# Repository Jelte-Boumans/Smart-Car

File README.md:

# Smart-Car
* Analyse bevat alle files die behoren tot de analyse van dit project
* Code bavat alle software geschreven voor dit project
* Schemas bevat alle versies van de schemas en PCBs voor dit project

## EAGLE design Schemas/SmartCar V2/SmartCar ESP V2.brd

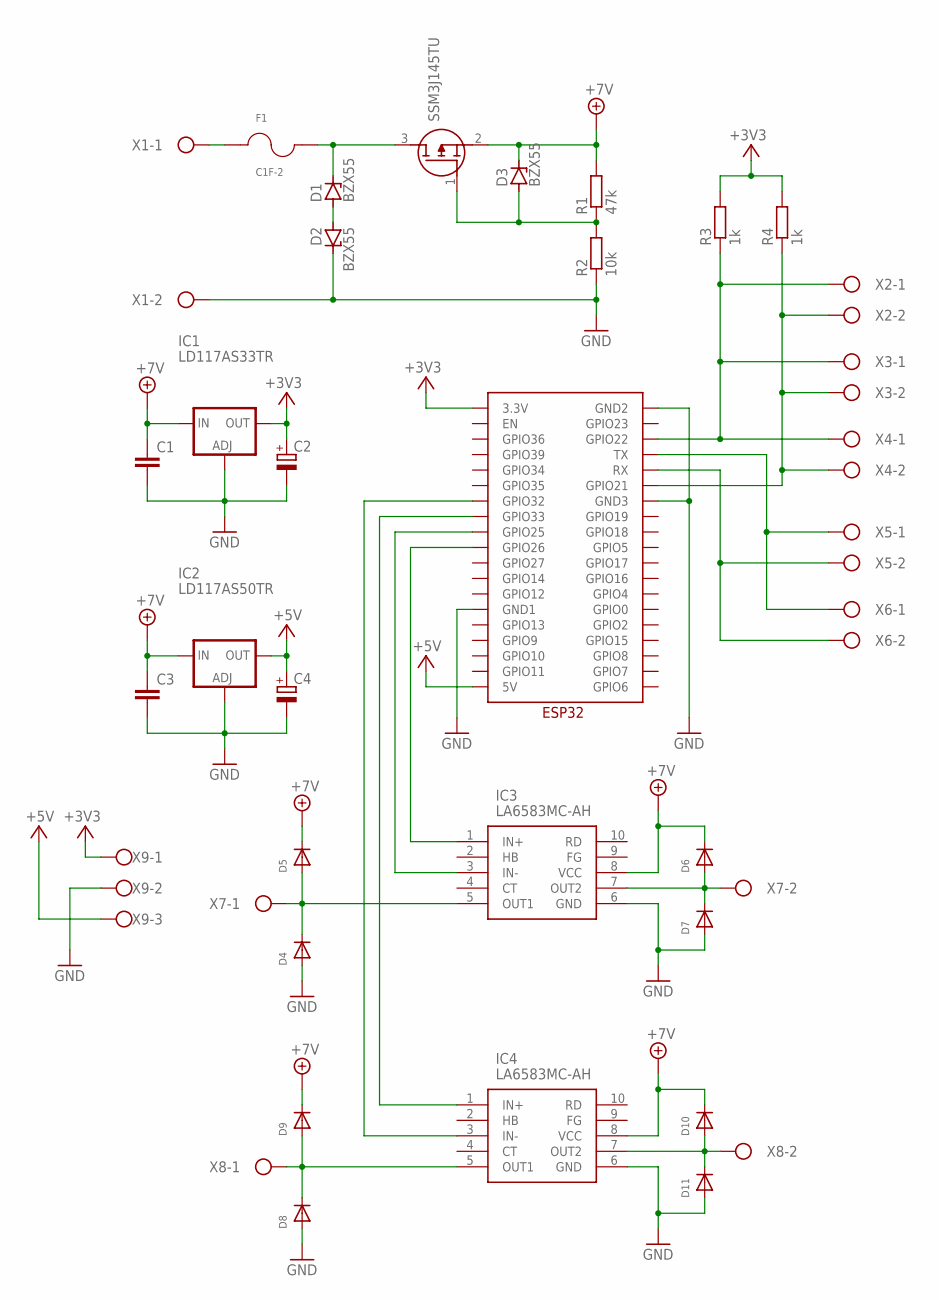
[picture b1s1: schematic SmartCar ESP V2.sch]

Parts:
C1, C3: C-EUC0805; C0805
C2, C4: CPOL-EUE2,5-6E; E2,5-6E
D1, D2, D3: BZX55; DO35Z10
D4, D5, D6, D7, D8, D9, D10, D11: DIODESMA; SMADIODE
F1: C1F-2; FUSC3215X83N
IC1: LD117AS33TR; SOT223
IC2: LD117AS50TR; SOT223
IC3, IC4: LA6583MC-AH; SOP100P620X155-10N
R1: 47k; R0805
R2: 10k; R0805
R3, R4: 1k; R0805
U$1: ESP32
U$2: SSM3J145TU; SOTFL65P210X75-3N
X1, X2, X3, X4, X5, X6, X7, X8: W237-102
X9: W237-103

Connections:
+3V3: C2.+, IC1.4 (OUT), R3.2, R4.2, U$1.3.3V, X9.1
+5V: C4.+, IC2.4 (OUT), U$1.5V, X9.3
+7V: C1.1, C3.1, D3.C, D5.C, D6.C, D9.C, D10.C, IC1.3 (IN), IC2.3 (IN), IC3.8 (VCC), IC4.8 (VCC), R1.2, U$2.2 (S)
GND: C1.2, C2.-, C3.2, C4.-, D2.C, D4.A, D7.A, D8.A, D11.A, IC1.1 (ADJ), IC2.1 (ADJ), IC3.6 (GND), IC4.6 (GND), R2.1, U$1.GND1, U$1.GND2, U$1.GND3, X1.2, X9.2
unnamed: F1.1, X1.1
unnamed: D1.A, D2.A
unnamed: D1.C, F1.2, U$2.3 (D)
unnamed: R4.1, U$1.GPIO21, X2.2, X3.2, X4.2
unnamed: U$1.TX, X5.1, X6.1
unnamed: D3.A, R1.1, R2.2, U$2.1 (G)
unnamed: R3.1, U$1.GPIO22, X2.1, X3.1, X4.1
unnamed: D4.C, D5.A, IC3.5 (OUT1), X7.1
unnamed: D6.A, D7.C, IC3.7 (OUT2), X7.2
unnamed: D10.A, D11.C, IC4.7 (OUT2), X8.2
unnamed: D8.C, D9.A, IC4.5 (OUT1), X8.1
unnamed: IC3.1 (IN+), U$1.GPIO26
unnamed: IC3.3 (IN-), U$1.GPIO25
unnamed: IC4.1 (IN+), U$1.GPIO33
unnamed: IC4.3 (IN-), U$1.GPIO32
unnamed: U$1.RX, X5.2, X6.2

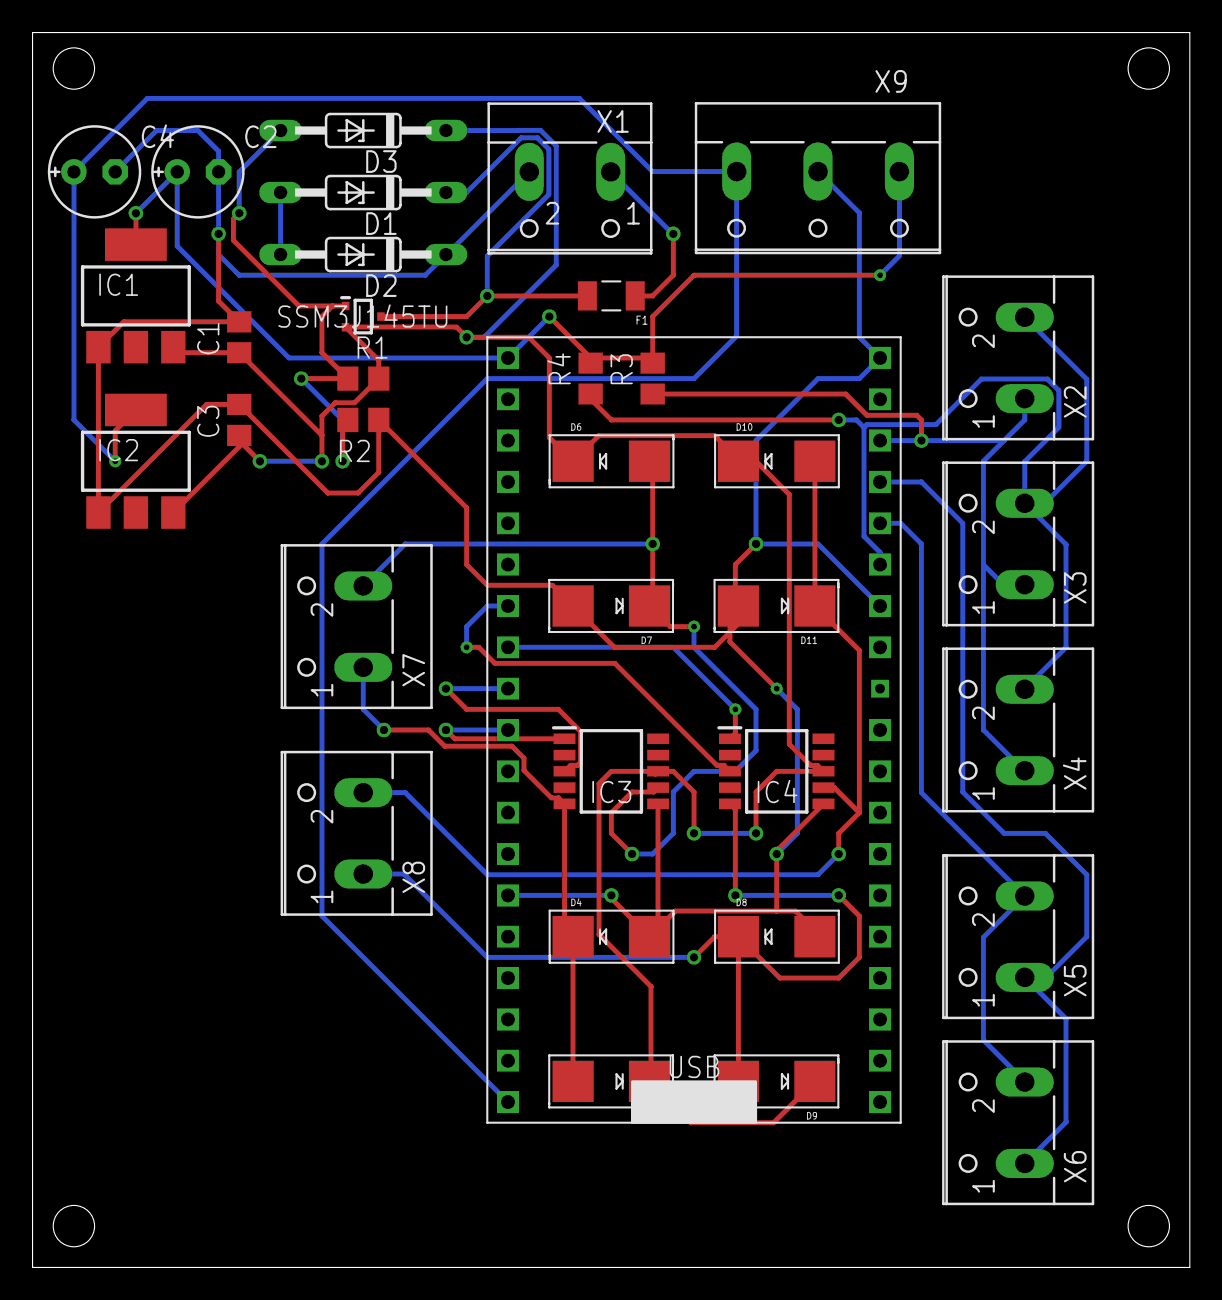
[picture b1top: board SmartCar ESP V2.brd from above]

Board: 2 copper layers, 71.1 x 75.9 mm, 35 parts (0 on the bottom side), 20 nets.

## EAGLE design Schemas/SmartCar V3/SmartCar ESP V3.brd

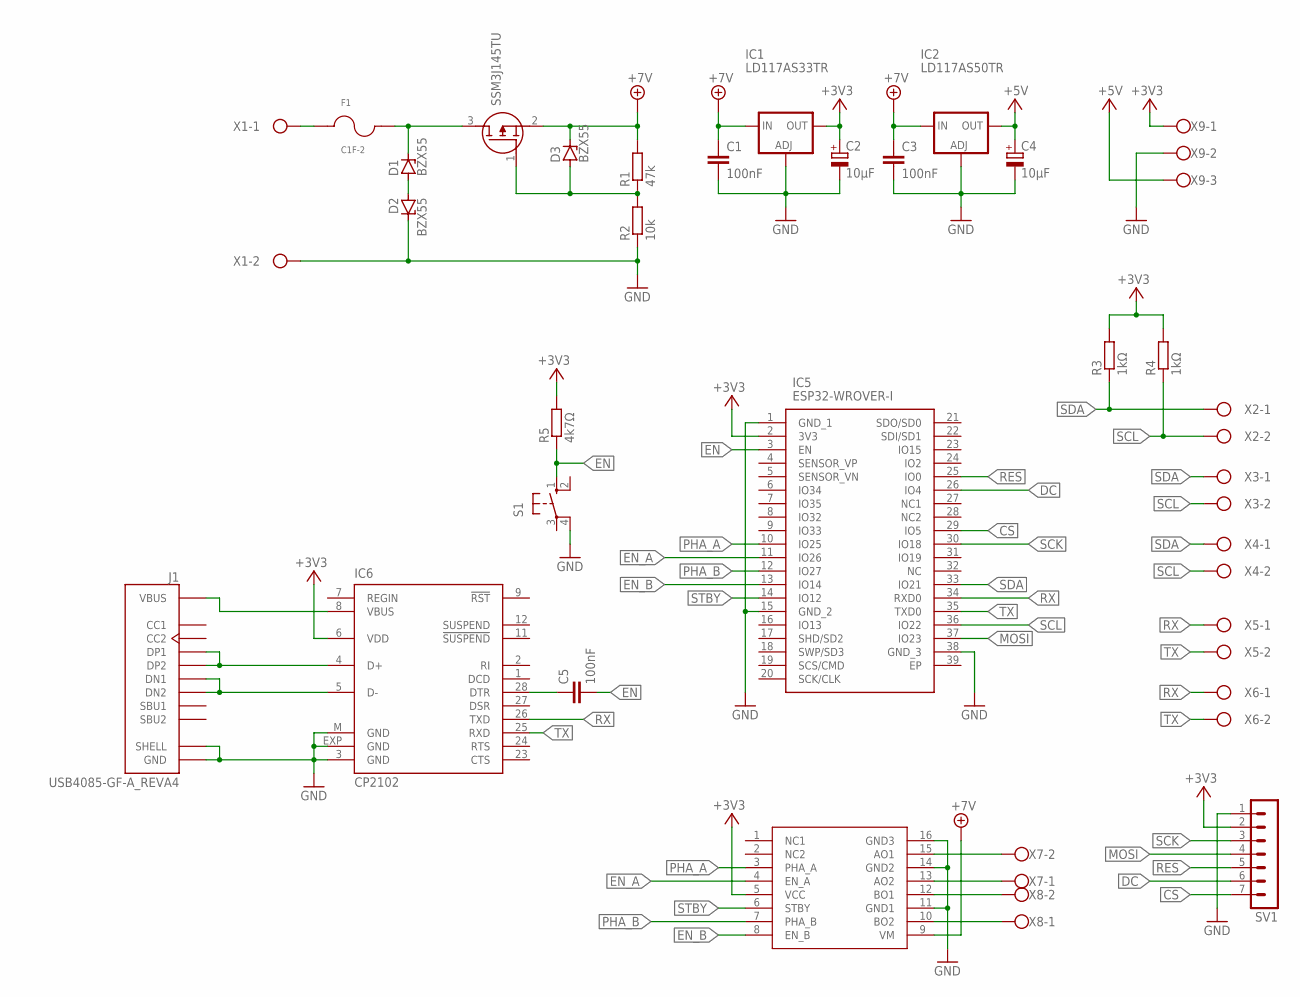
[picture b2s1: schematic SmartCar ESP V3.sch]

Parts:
C1, C3, C5: 100nF; C0805
C2, C4: 10µF; E2,5-6E
D1, D2, D3: BZX55; DO35Z10
F1: C1F-2; FUSC3215X83N
IC1: LD117AS33TR; SOT223
IC2: LD117AS50TR; SOT223
IC5: ESP32-WROVER-I; ESP32WROVERI
IC6: CP2102; MLP28
J1: USB4085-GF-A_REVA4; GCT_USB4085-GF-A_REVA4
R1: 47k; R0805
R2: 10k; R0805
R3, R4: 1kΩ; R0805
R5: 4k7Ω; R0805
S1: 10-XX; B3F-10XX
SV1: MA07-1
U$1: TC78H621FNG; SOP65P640X110-16N
U$2: SSM3J145TU; SOTFL65P210X75-3N
X1, X2, X3, X4, X5, X6, X7, X8: W237-102
X9: W237-103

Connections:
+3V3: C2.+, IC1.4 (OUT), IC5.2 (3V3), IC6.6 (VDD), R3.2, R4.2, R5.2, SV1.2, U$1.5 (VCC), X9.1
+5V: C4.+, IC2.4 (OUT), X9.3
+7V: C1.1, C3.1, D3.C, IC1.3 (IN), IC2.3 (IN), R1.2, U$1.9 (VM), U$2.2 (S)
CS: IC5.29 (IO5), SV1.7
DC: IC5.26 (IO4), SV1.6
EN: C5.2, IC5.3 (EN), R5.1, S1.1 (S)
EN_A: IC5.11 (IO26), U$1.4 (EN_A)
EN_B: IC5.13 (IO14), U$1.8 (EN_B)
GND: C1.2, C2.-, C3.2, C4.-, D2.C, IC1.1 (ADJ), IC2.1 (ADJ), IC5.1 (GND_1), IC5.15 (GND_2), IC5.38 (GND_3), IC6.3 (GND), IC6.EXP (GND), IC6.M (GND), J1.A1 (GND), J1.A12 (GND), J1.B1 (GND), J1.B12 (GND), J1.P1 (SHELL), J1.P2 (SHELL), J1.P3 (SHELL), J1.P4 (SHELL), R2.1, S1.4 (P1), SV1.1, U$1.11 (GND1), U$1.14 (GND2), U$1.16 (GND3), X1.2, X9.2
MOSI: IC5.37 (IO23), SV1.4
unnamed: F1.1, X1.1
unnamed: D1.A, D2.A
unnamed: D1.C, F1.2, U$2.3 (D)
unnamed: IC6.5 (D-), J1.A7 (DN1), J1.B7 (DN2)
unnamed: IC6.4 (D+), J1.A6 (DP1), J1.B6 (DP2)
unnamed: C5.1, IC6.28 (DTR)
unnamed: D3.A, R1.1, R2.2, U$2.1 (G)
unnamed: U$1.15 (AO1), X7.2
unnamed: U$1.13 (AO2), X7.1
unnamed: U$1.12 (BO1), X8.2
unnamed: U$1.10 (BO2), X8.1
unnamed: IC6.8 (VBUS), J1.A4 (VBUS), J1.A9 (VBUS), J1.B4 (VBUS), J1.B9 (VBUS)
PHA_A: IC5.10 (IO25), U$1.3 (PHA_A)
PHA_B: IC5.12 (IO27), U$1.7 (PHA_B)
RES: IC5.25 (IO0), SV1.5
RX: IC5.34 (RXD0), IC6.26 (TXD), X5.1, X6.1
SCK: IC5.30 (IO18), SV1.3
SCL: IC5.36 (IO22), R4.1, X2.2, X3.2, X4.2
SDA: IC5.33 (IO21), R3.1, X2.1, X3.1, X4.1
STBY: IC5.14 (IO12), U$1.6 (STBY)
TX: IC5.35 (TXD0), IC6.25 (RXD), X5.2, X6.2

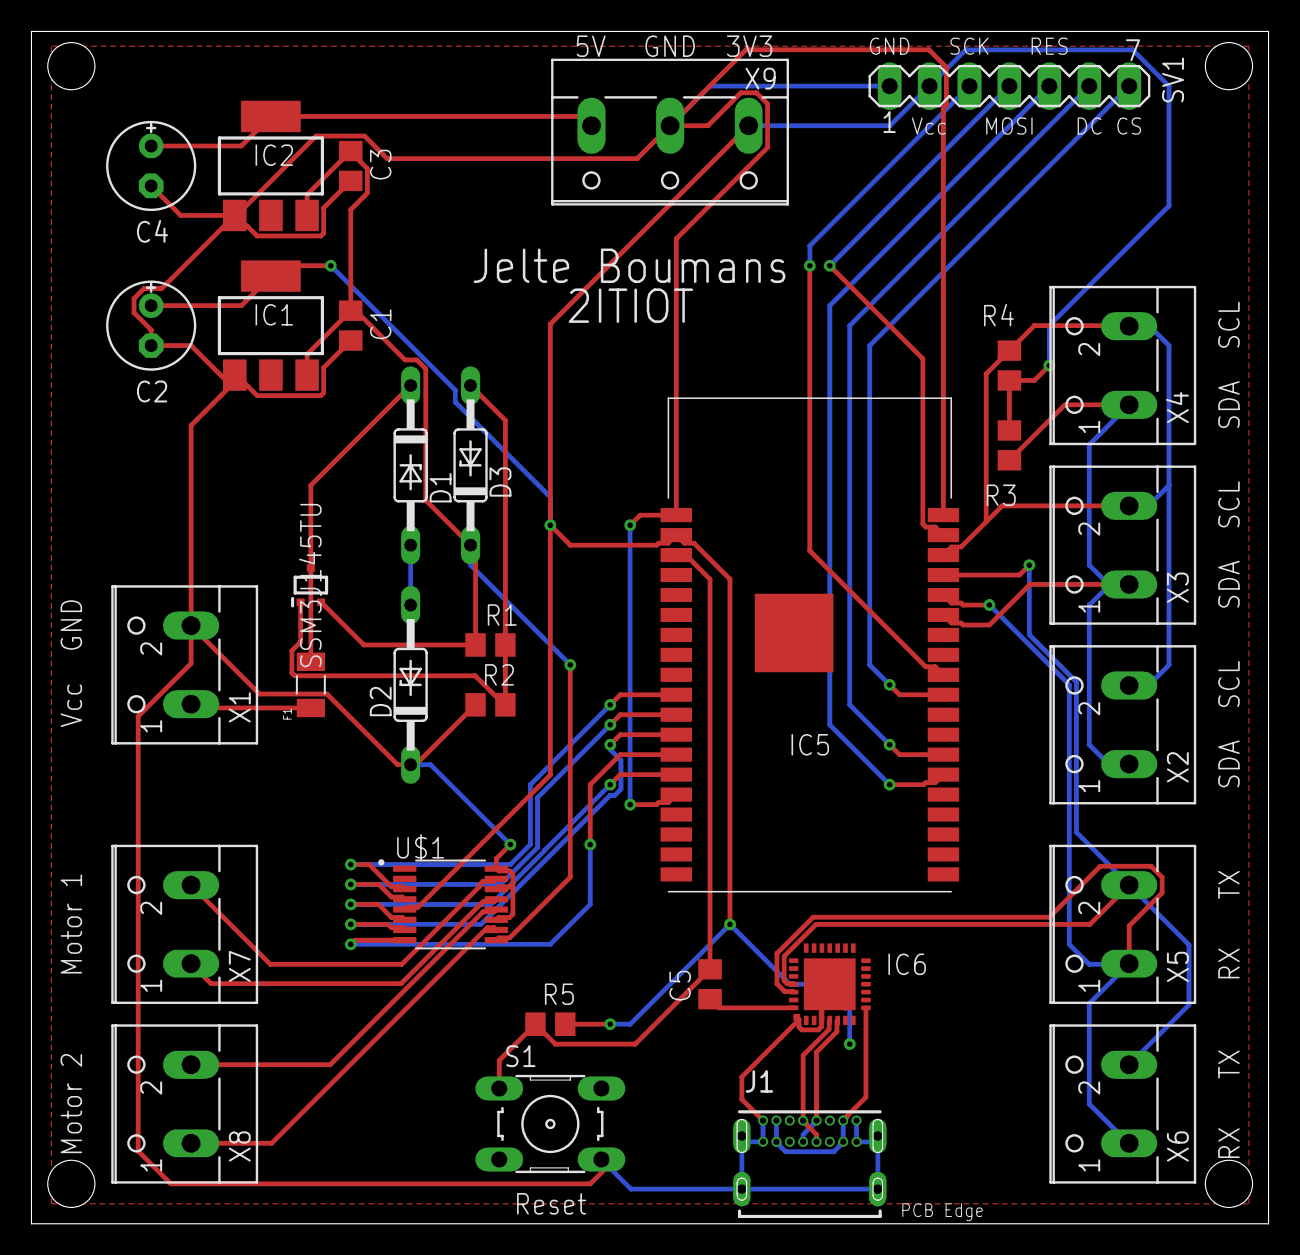
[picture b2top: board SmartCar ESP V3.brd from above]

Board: 2 copper layers, 78.7 x 75.9 mm, 32 parts (0 on the bottom side), 31 nets.

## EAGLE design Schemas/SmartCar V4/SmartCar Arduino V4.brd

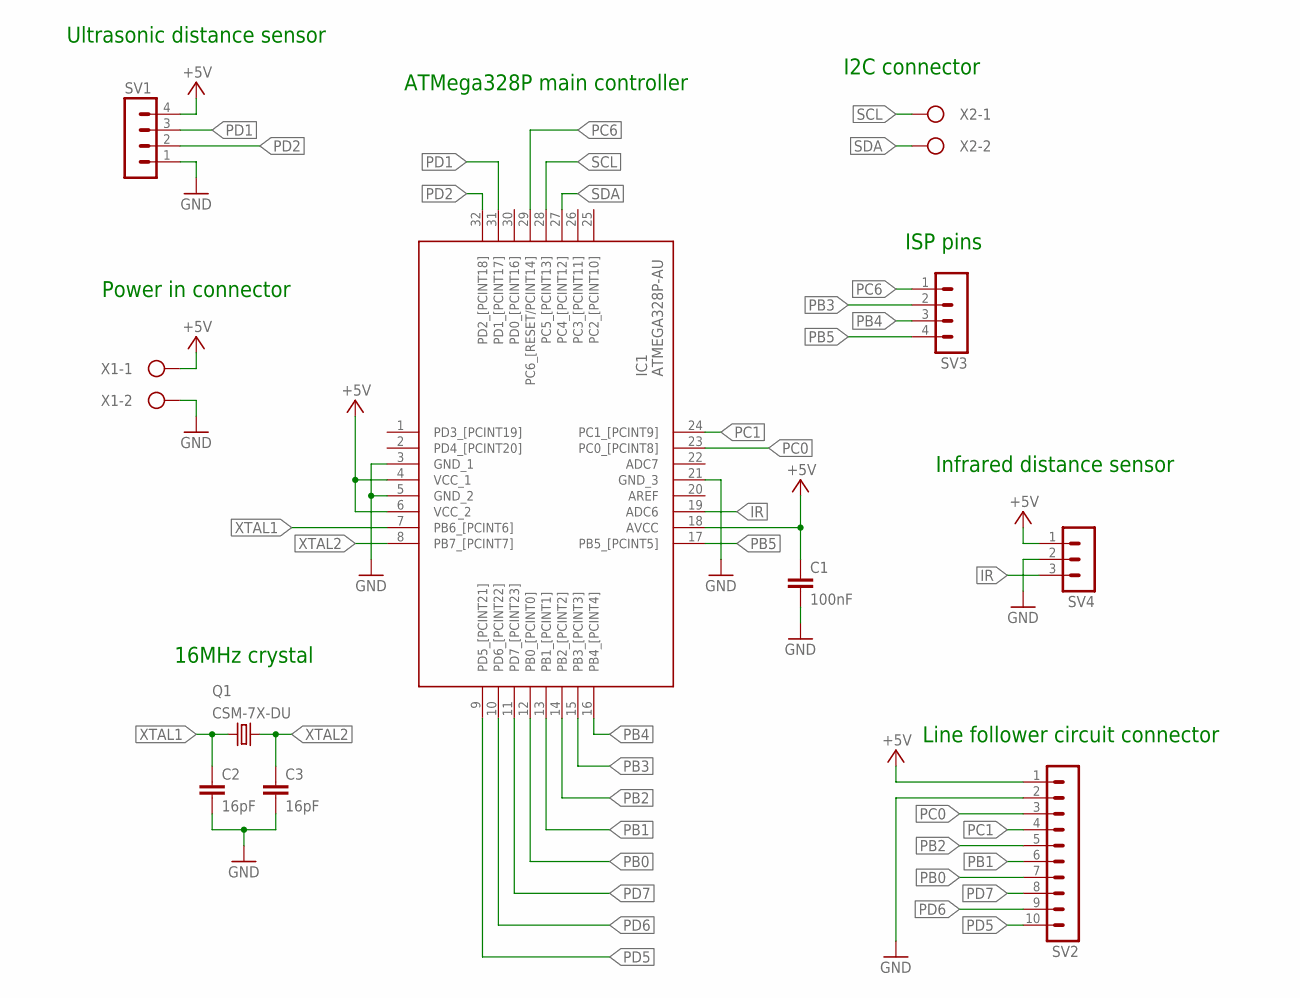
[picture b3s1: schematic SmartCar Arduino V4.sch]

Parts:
C1: 100nF; C0805
C2, C3: 16pF; C0805
IC1: ATMEGA328P-AU; QFP80P900X900X120-32N
Q1: CSM-7X-DU
SV1, SV3: 0; MA04-1
SV2: 0; MA10-1
SV4: 0; MA03-1
X1, X2: 0; W237-102

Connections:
+5V: C1.1, IC1.4 (VCC_1), IC1.6 (VCC_2), IC1.18 (AVCC), SV1.4, SV2.1, SV4.1, X1.1
GND: C1.2, C2.2, C3.2, IC1.3 (GND_1), IC1.5 (GND_2), IC1.21 (GND_3), SV1.1, SV2.2, SV4.2, X1.2
IR: IC1.19 (ADC6), SV4.3
PB0: IC1.12 (PB0_[PCINT0]), SV2.7
PB1: IC1.13 (PB1_[PCINT1]), SV2.6
PB2: IC1.14 (PB2_[PCINT2]), SV2.5
PB3: IC1.15 (PB3_[PCINT3]), SV3.2
PB4: IC1.16 (PB4_[PCINT4]), SV3.3
PB5: IC1.17 (PB5_[PCINT5]), SV3.4
PC0: IC1.23 (PC0_[PCINT8]), SV2.3
PC1: IC1.24 (PC1_[PCINT9]), SV2.4
PC6: IC1.29 (PC6_[RESET/PCINT14]), SV3.1
PD1: IC1.31 (PD1_[PCINT17]), SV1.3
PD2: IC1.32 (PD2_[PCINT18]), SV1.2
PD5: IC1.9 (PD5_[PCINT21]), SV2.10
PD6: IC1.10 (PD6_[PCINT22]), SV2.9
PD7: IC1.11 (PD7_[PCINT23]), SV2.8
SCL: IC1.28 (PC5_[PCINT13]), X2.1
SDA: IC1.27 (PC4_[PCINT12]), X2.2
XTAL1: C2.1, IC1.7 (PB6_[PCINT6]), Q1.1
XTAL2: C3.1, IC1.8 (PB7_[PCINT7]), Q1.2

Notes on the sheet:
Ultrasonic distance sensor
Power in connector
16MHz crystal
ATMega328P main controller
I2C connector
ISP pins
Infrared distance sensor
Line follower circuit connector

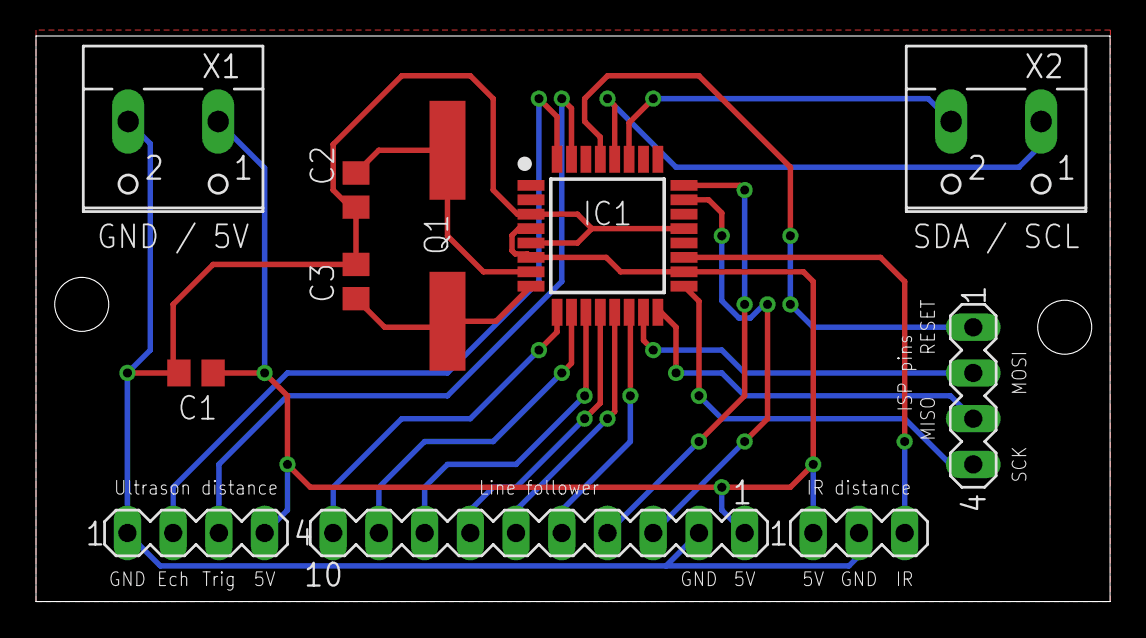
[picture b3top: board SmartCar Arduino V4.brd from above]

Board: 2 copper layers, 59.7 x 31.4 mm, 11 parts (0 on the bottom side), 21 nets.

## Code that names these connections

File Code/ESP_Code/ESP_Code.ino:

#include <WiFi.h>
#include <PubSubClient.h>
#include <Wire.h>
#include <ESP32Servo.h>
#include <Adafruit_GFX.h>
#include <Adafruit_SSD1306.h>

// OLED display width and height, in pixels - DO NOT CHANGE
#define SCREEN_WIDTH 128
#define SCREEN_HEIGHT 64

// Declaration for SSD1306 display connected using software SPI - DO NOT CHANGE
#define OLED_MOSI   23
#define OLED_CLK   18
#define OLED_DC    4
#define OLED_CS    5
#define OLED_RESET 0

// The pins the servo motors are connected to - DO NOT CHANGE
#define SERVO1 1
#define SERVO2 2

// The pins the motor controller is connected to - DO NOT CHANGE
#define PHA_A 25  // Left motor
#define EN_A 26

#define PHA_B 27  // Right motor
#define EN_B 14

#define STANDBY 12

// Motor channels
#define MOTOR_L 0
#define MOTOR_R 0

// PWM Settings - DO NOT CHANGE
#define PWM_FREQUENCY 500
#define PWM_RESOLUTION 8
#define PWM_MAX_DC 255

// Thresholds for the distance sensors
#define OBSTACLE_THRESHOLD_CM 3
#define OBSTACLE_THRESHOLD_BYTE 100

// Change ssid and password to the ones of the network you want to connect to
char* ssid = "*****";
char* password = "*****";
char* mqtt_server = "mqtt.luytsm.be";

// Variables to save the data recieved from node-red dashboard
String mode = "";
String driveDirection = "";
byte driveSpeed = 0;
byte sensorData[3] = {};

// Objects for Wifi, MQTT, servos and OLED
WiFiClient espClient;
PubSubClient client(espClient);
Servo barrier1;
Servo barrier2;
Adafruit_SSD1306 display(SCREEN_WIDTH, SCREEN_HEIGHT, OLED_MOSI, OLED_CLK, OLED_DC, OLED_RESET, OLED_CS);

void setup() {
  Serial.begin(115200);
  setup_wifi();
  client.setServer(mqtt_server, 1883);
  client.setCallback(callback);

  barrier1.attach(SERVO1);
  barrier2.attach(SERVO2);

  barrier1.write(90);
  barrier2.write(90);

  ledcSetup(MOTOR_L, PWM_FREQUENCY, PWM_RESOLUTION);
  ledcSetup(MOTOR_R, PWM_FREQUENCY, PWM_RESOLUTION);

  ledcAttachPin(EN_A, MOTOR_L);
  ledcAttachPin(EN_B, MOTOR_R);

  Wire.begin();
}

void setup_wifi() {
  delay(10);
  Serial.println();
  Serial.print("Connecting to ");
  Serial.println(ssid);

  WiFi.begin(ssid, password);

  while (WiFi.status() != WL_CONNECTED) {
    delay(500);
    Serial.print(".");
  }

  Serial.println("");
  Serial.println("WiFi connected");
  Serial.println("IP address: ");
  Serial.println(WiFi.localIP());
}

void callback(char* topic, byte* payload, unsigned int length) {
  Serial.print("Message arrived on topic: ");
  Serial.print(topic);
  Serial.print(". Message: ");
  String data;
  
  for (int i = 0; i < length; i++) {
    Serial.print((char)payload[i]);
    data += (char)payload[i];
  }
  Serial.println();

  if(String(topic) == "/jelte/mode")
    mode = data;
    
  else if (String(topic) == "/jelte/standby") {
    if(data == "1")
      digitalWrite(STANDBY, LOW);
    else
      digitalWrite(STANDBY, HIGH);  
  }
      
  else if (String(topic) == "/jelte/barriers") {
    if(data == "omhoog1")
      barrier1.write(90);
    else if (data == "omlaag1")
      barrier1.write(0);

    if(data == "omhoog2")
      barrier2.write(90);
    else if (data == "omlaag2")
      barrier2.write(0);
  }
  
  else if (String(topic) == "/jelte/speed")
    driveSpeed = data.toInt();
    
  else if (String(topic) == "/jelte/dir")
    driveDirection = data;
    
  else {
    Serial.println("Unknown topic...");
    return;
  }
}

void reconnect() {
  while (!client.connected()) {
    Serial.print("Attempting MQTT connection...");
    if (client.connect("ESP8266Client")) {
      Serial.println("connected");
      client.subscribe("/jelte/mode");
      client.subscribe("/jelte/standby");
      client.subscribe("/jelte/barriers");
      client.subscribe("/jelte/dir");
      client.subscribe("/jelte/speed");
      Serial.println("Subscribed");
    } 
    else {
      Serial.print("failed, rc=");
      Serial.print(client.state());
      Serial.println(" try again in 5 seconds");
      delay(5000);
    }
  }
}

void loop() {
  if (!client.connected()) {
    reconnect();
  }
  client.loop();
 
  if(mode == "manueel")
    manualControl();
    
  else if (mode == "automatisch")
    automaticControl();
}

// Code for when you want to control the car manually
void manualControl() {
  driveSpeed = map(driveSpeed, 0, 100, 0, 255); // Change te recieved percent value to byte
  
  if(driveDirection == "stop") {
    // Stop both motors
    ledcWrite(MOTOR_L, 0);
    ledcWrite(MOTOR_R, 0);
  }

  else if(driveDirection == "vooruit") {
    // Both motors spin forwards
    digitalWrite(PHA_A, HIGH);
    digitalWrite(PHA_B, HIGH);

    // Turn motors at recieved speeds
    ledcWrite(MOTOR_L, driveSpeed);
    ledcWrite(MOTOR_R, driveSpeed);
  }

  else if(driveDirection == "links") {
    // Both motors spin forwards
    digitalWrite(PHA_A, HIGH);
    digitalWrite(PHA_B, HIGH);

    // Turn right motor at recieved speed
    ledcWrite(MOTOR_L, 0);
    ledcWrite(MOTOR_R, driveSpeed);
  }

  else if(driveDirection == "rechts") {
    // Both motors spin forwards
    digitalWrite(PHA_A, HIGH);
    digitalWrite(PHA_B, HIGH);

    // Turn left motor at recieved speed
    ledcWrite(MOTOR_L, driveSpeed);
    ledcWrite(MOTOR_R, 0);
  }

  else if(driveDirection == "achteruit") {
    // Both motors spin backwards
    digitalWrite(PHA_A, LOW);
    digitalWrite(PHA_B, LOW);

    // Turn motors at recieved speeds
    ledcWrite(MOTOR_L, driveSpeed);
    ledcWrite(MOTOR_R, driveSpeed);
  }

  else if(driveDirection == "links-vooruit") {
    // Both motors spin forwards
    digitalWrite(PHA_A, HIGH);
    digitalWrite(PHA_B, HIGH);

    // Turn right motor at recieved speed and left motor at half
    ledcWrite(MOTOR_L, driveSpeed/2);
    ledcWrite(MOTOR_R, driveSpeed);
  }

  else if(driveDirection == "rechts-vooruit") {
    // Both motors spin forwards
    digitalWrite(PHA_A, HIGH);
    digitalWrite(PHA_B, HIGH);

    // Turn left motor at recieved speed and right motor at half
    ledcWrite(MOTOR_L, driveSpeed);
    ledcWrite(MOTOR_R, driveSpeed/2);
  }

  else if(driveDirection == "links-achter") {
    // Both motors spin backwards
    digitalWrite(PHA_A, LOW);
    digitalWrite(PHA_B, LOW);

    // Turn right motor at recieved speed and left motor at half
    ledcWrite(MOTOR_L, driveSpeed/2);
    ledcWrite(MOTOR_R, driveSpeed);
  }

  else if(driveDirection == "rechts-achter") {
    // Both motors spin backwards
    digitalWrite(PHA_A, LOW);
    digitalWrite(PHA_B, LOW);

    // Turn left motor at recieved speed and right motor at half
    ledcWrite(MOTOR_L, driveSpeed);
    ledcWrite(MOTOR_R, driveSpeed/2);
  }
}

// Code for when you want to control the car automatically
void automaticControl() {
  // 3 bytes from device 8
  Wire.requestFrom(8, 3);
  // Wait until the 3 bytes are here
  while(Wire.available() < 3) {}

  // Read and save sensor data
  for(byte i = 0; i < 3; i++) {
    sensorData[i] = Wire.read(); 
  }

  // Stop if there is an obstacle in front of the car
  if(sensorData[0] >= OBSTACLE_THRESHOLD_BYTE || sensorData[1] <= OBSTACLE_THRESHOLD_CM) {
    // Stop both motors
    ledcWrite(MOTOR_L, 0);
    ledcWrite(MOTOR_R, 0);
  }
  // If there is no obstacle, start linetracker
  else {
    // Both motors spin forwards
    digitalWrite(PHA_A, HIGH);
    digitalWrite(PHA_B, HIGH);
    if(sensorData[2] & 0b00111100 <= 0b00100000 && sensorData[2] & 0b00111100 >= 0b00000100) {  // Line is straight
      // Turn motors at recieved speed
      ledcWrite(MOTOR_L, driveSpeed);
      ledcWrite(MOTOR_R, driveSpeed);
    }
    else if(sensorData[2] & 0b00000111 <= 0b00000111) { // Line goes to the right
      // Turn left motor at recieved speed and right motor at half
      ledcWrite(MOTOR_L, driveSpeed);
      ledcWrite(MOTOR_R, driveSpeed/2);
    }
    else if(sensorData[2] & 0b11100000 >= 0b00100000) { // Line goes to the left
      // Turn right motor at recieved speed and left motor at half
      ledcWrite(MOTOR_L, driveSpeed/2);
      ledcWrite(MOTOR_R, driveSpeed);
    }
  }
}

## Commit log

2022-05-04 Create test
